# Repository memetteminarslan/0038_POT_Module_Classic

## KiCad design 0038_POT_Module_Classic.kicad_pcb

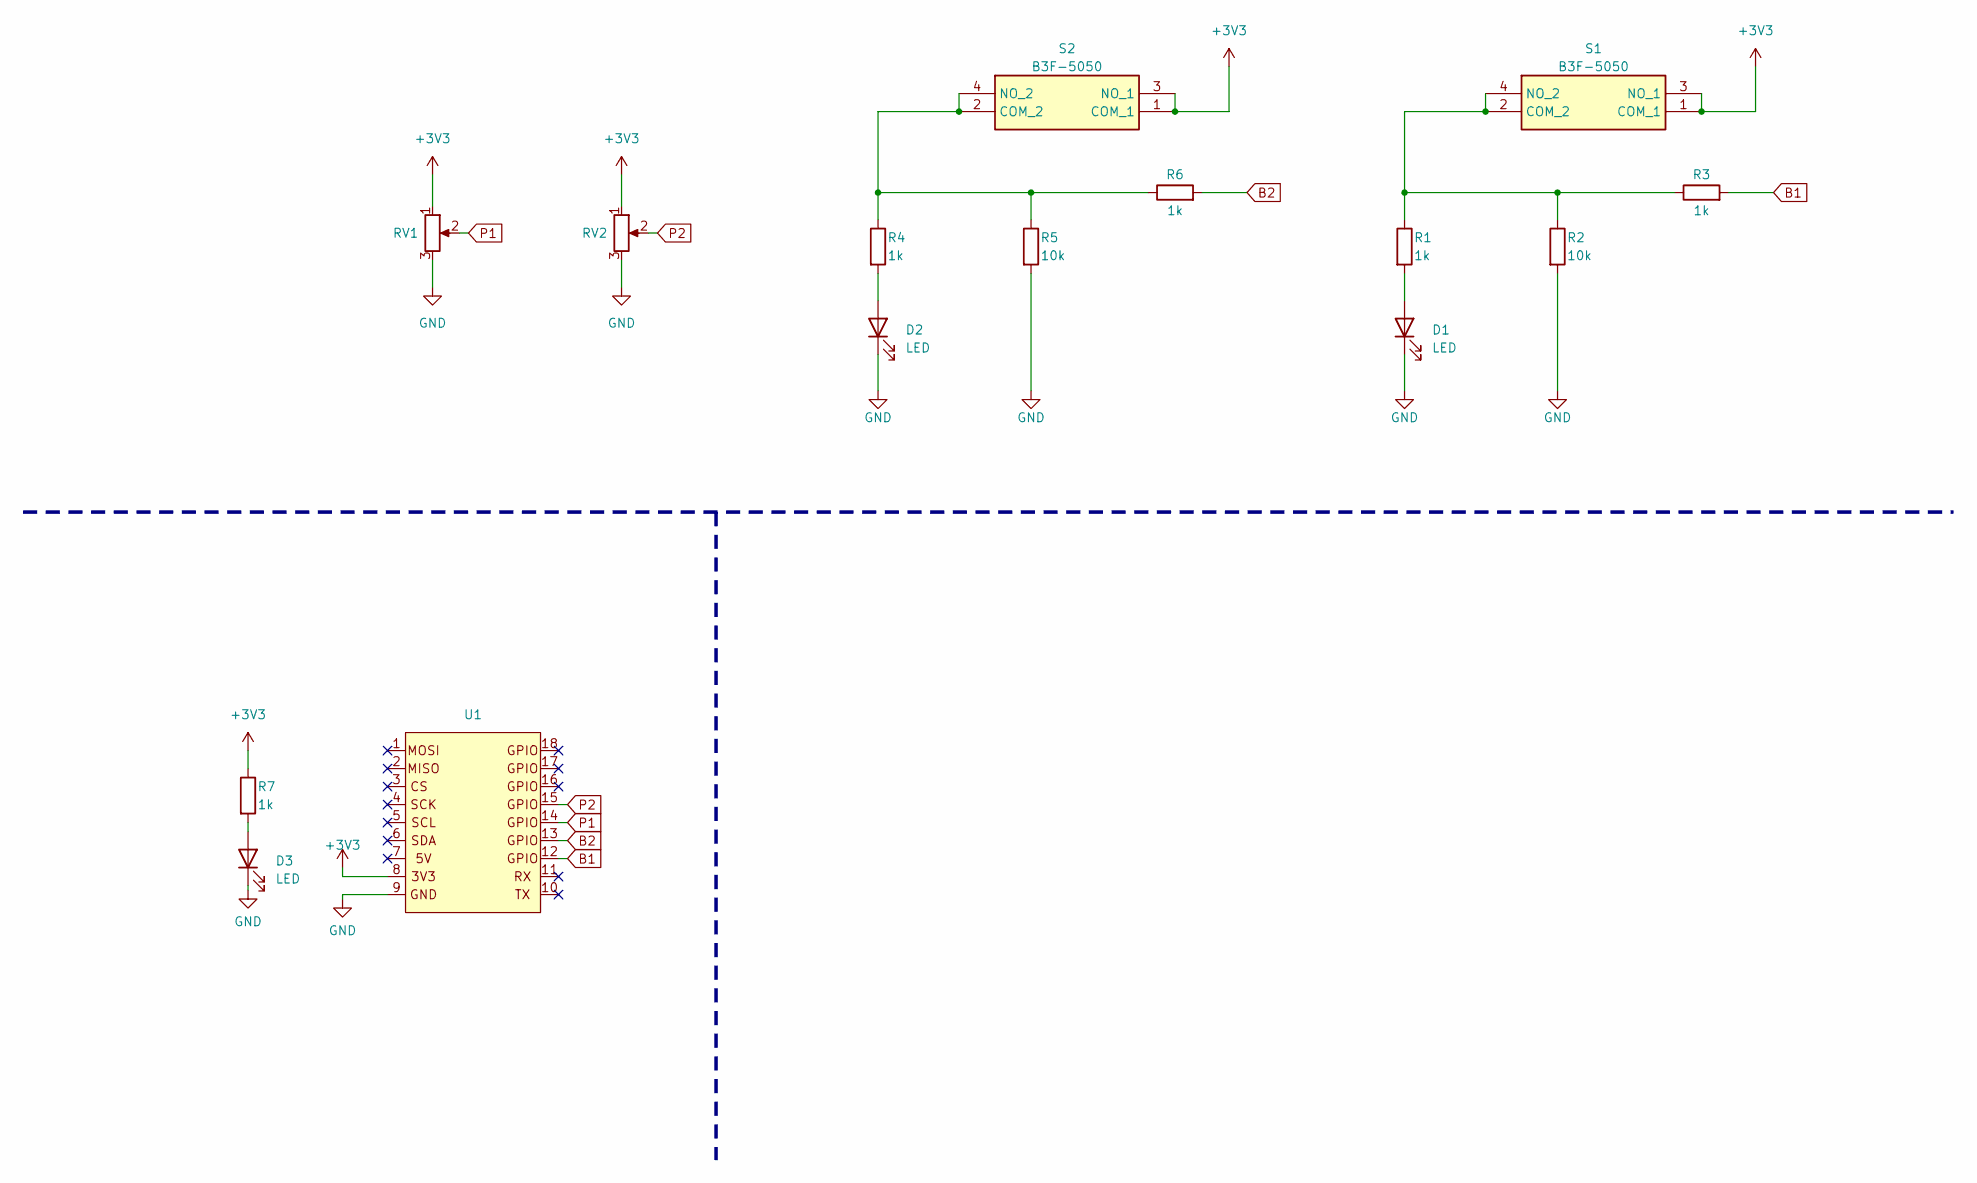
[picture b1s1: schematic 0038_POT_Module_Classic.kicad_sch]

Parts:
D1, D2, D3: LED; LED_0603_1608Metric
R1, R3, R4, R6, R7: 1k; R_0603_1608Metric
R2, R5: 10k; R_0603_1608Metric
RV1, RV2: R_Potentiometer; RK09D113F25C0B504
S1, S2: B3F-5050; B3F-4055; Mouser Part Number 653-B3F-5050
U1: pin_header_5-3

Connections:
+3V3: R7.1, RV1.1, RV2.1, S1.1 (COM_1), S1.3 (NO_1), S2.1 (COM_1), S2.3 (NO_1), U1.8
B1: R3.2, U1.12
B2: R6.2, U1.13
GND: D1.1 (K), D2.1 (K), D3.1 (K), R2.2, R5.2, RV1.3, RV2.3, U1.9
unnamed: D1.2 (A), R1.2
unnamed: D2.2 (A), R4.2
unnamed: D3.2 (A), R7.2
unnamed: R1.1, R2.1, R3.1, S1.2 (COM_2), S1.4 (NO_2)
unnamed: R4.1, R5.1, R6.1, S2.2 (COM_2), S2.4 (NO_2)
P1: RV1.2, U1.14
P2: RV2.2, U1.15

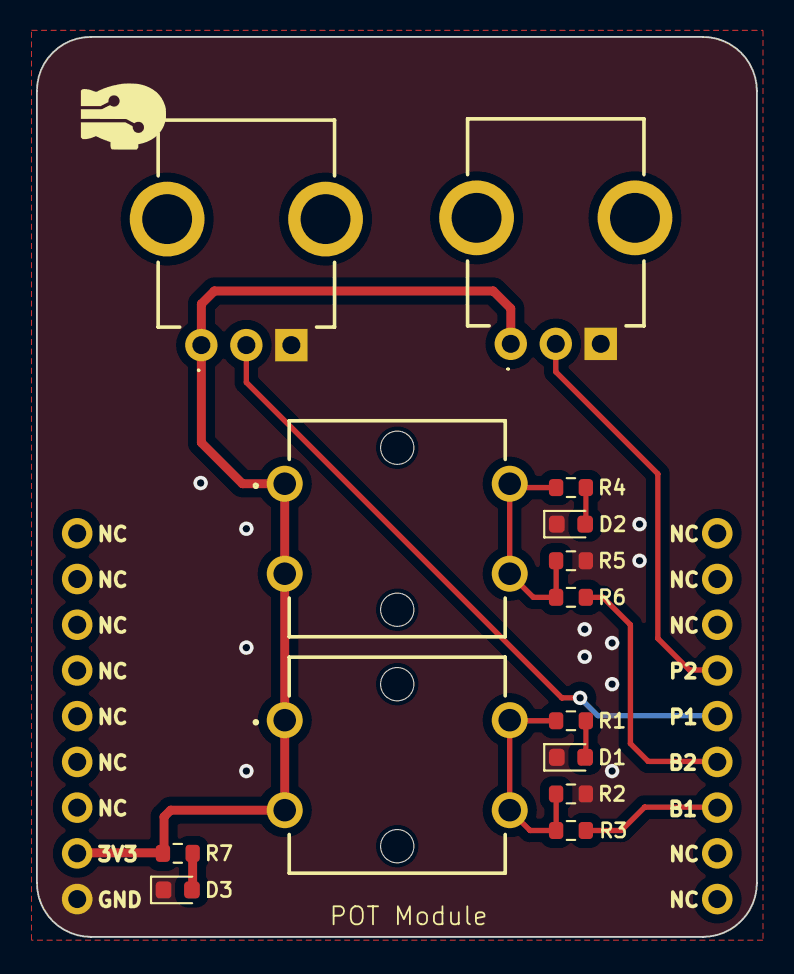
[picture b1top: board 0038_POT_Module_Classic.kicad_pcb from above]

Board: 2 copper layers, 40.0 x 50.0 mm, 15 parts (0 on the bottom side), 11 nets.
